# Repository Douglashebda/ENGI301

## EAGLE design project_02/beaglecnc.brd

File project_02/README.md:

**Board Prototype**

A PCB designed for the Desktop CNC design outlined here:

https://www.hackster.io/dah8/pocketbeagle-cnc-using-beagleg-070f2f

This board was designed for ENGI301 @RiceUni

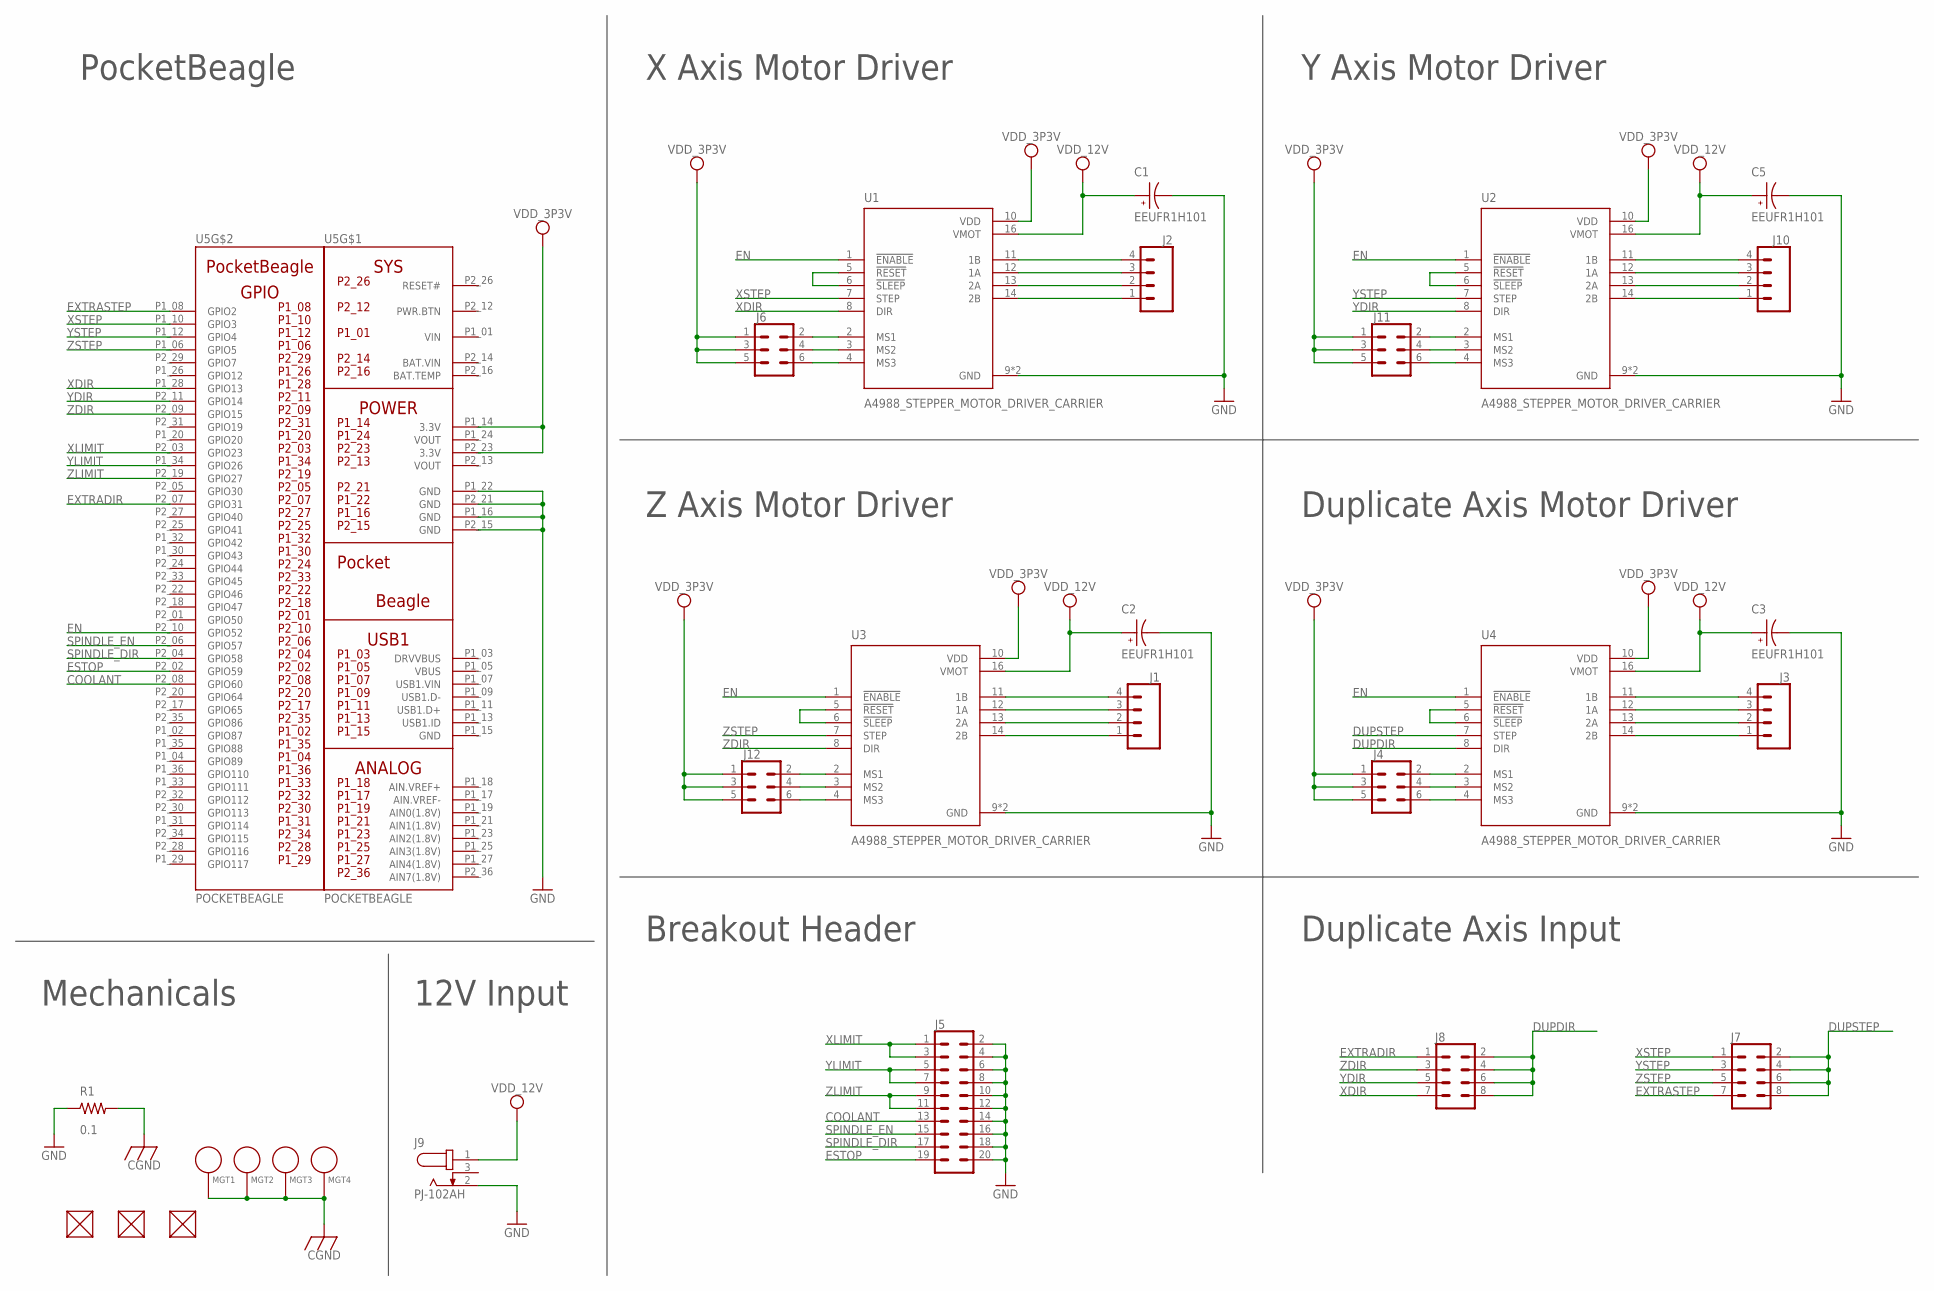
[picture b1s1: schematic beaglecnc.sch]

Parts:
C1, C2, C3, C5: EEUFR1H101; CAPPRD350W60D800H1150
FUD1, FUD2, FUD3: FIDUCIAL; FIDUCIAL_40MIL
J1, J2, J3, J10: CONN_04PTH; 1X04
J4, J6, J11, J12: CONN_03X22X3_SILK_MALE_PTH; 2X3
J5: CONN_10X2; 2X10
J7, J8: CONN_04X2; 2X4
J9: PJ-102AH; CUI_PJ-102AH
MGT1, MGT2, MGT3, MGT4: MOUNTING_HOLE
R1: 0.1; R0805
U1, U2, U3, U4: A4988_STEPPER_MOTOR_DRIVER_CARRIER; MODULE_A4988_STEPPER_MOTOR_DRIVER_CARRIER
U5: POCKETBEAGLE

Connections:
BAT.VIN: U5.P2_14 (BAT.VIN)
CGND: MGT1.P$1, MGT2.P$1, MGT3.P$1, MGT4.P$1, R1.2
COOLANT: J5.13, U5.P2_08 (GPIO60)
DUPDIR: J8.2, J8.4, J8.6, J8.8, U4.8 (DIR)
DUPSTEP: J7.2, J7.4, J7.6, J7.8, U4.7 (STEP)
EN: U1.1 (!ENABLE), U2.1 (!ENABLE), U3.1 (!ENABLE), U4.1 (!ENABLE), U5.P2_10 (GPIO52)
ESTOP: J5.19, U5.P2_02 (GPIO59)
EXTRADIR: J8.1, U5.P2_07 (GPIO31)
EXTRASTEP: J7.7, U5.P1_08 (GPIO2)
GND: C1.N, C2.N, C3.N, C5.N, J5.2, J5.4, J5.6, J5.8, J5.10, J5.12, J5.14, J5.16, J5.18, J5.20, J9.2, R1.1, U1.9 (GND), U1.15 (GND), U2.9 (GND), U2.15 (GND), U3.9 (GND), U3.15 (GND), U4.9 (GND), U4.15 (GND), U5.P1_16 (GND), U5.P1_22 (GND), U5.P2_15 (GND), U5.P2_21 (GND)
unnamed: J2.4, U1.11 (1B)
unnamed: J2.3, U1.12 (1A)
unnamed: J2.2, U1.13 (2A)
unnamed: J2.1, U1.14 (2B)
unnamed: U1.5 (!RESET), U1.6 (!SLEEP)
unnamed: J6.2, U1.2 (MS1)
unnamed: J6.4, U1.3 (MS2)
unnamed: J6.6, U1.4 (MS3)
unnamed: J10.4, U2.11 (1B)
unnamed: J10.3, U2.12 (1A)
unnamed: J10.2, U2.13 (2A)
unnamed: J10.1, U2.14 (2B)
unnamed: U2.5 (!RESET), U2.6 (!SLEEP)
unnamed: J11.2, U2.2 (MS1)
unnamed: J11.4, U2.3 (MS2)
unnamed: J11.6, U2.4 (MS3)
unnamed: J1.4, U3.11 (1B)
unnamed: J1.3, U3.12 (1A)
unnamed: J1.2, U3.13 (2A)
unnamed: J1.1, U3.14 (2B)
unnamed: U3.5 (!RESET), U3.6 (!SLEEP)
unnamed: J12.2, U3.2 (MS1)
unnamed: J12.4, U3.3 (MS2)
unnamed: J12.6, U3.4 (MS3)
unnamed: J3.4, U4.11 (1B)
unnamed: J3.3, U4.12 (1A)
unnamed: J3.2, U4.13 (2A)
unnamed: J3.1, U4.14 (2B)
unnamed: U4.5 (!RESET), U4.6 (!SLEEP)
unnamed: J4.2, U4.2 (MS1)
unnamed: J4.4, U4.3 (MS2)
unnamed: J4.6, U4.4 (MS3)
SPINDLE_DIR: J5.17, U5.P2_04 (GPIO58)
SPINDLE_EN: J5.15, U5.P2_06 (GPIO57)
VDD_3P3V: J4.1, J4.3, J4.5, J6.1, J6.3, J6.5, J11.1, J11.3, J11.5, J12.1, J12.3, J12.5, U1.10 (VDD), U2.10 (VDD), U3.10 (VDD), U4.10 (VDD), U5.P1_14 (3.3V), U5.P2_23 (3.3V)
VDD_12V: C1.P, C2.P, C3.P, C5.P, J9.1, U1.16 (VMOT), U2.16 (VMOT), U3.16 (VMOT), U4.16 (VMOT)
VIN: U5.P1_01 (VIN)
VOUT: U5.P1_24 (VOUT), U5.P2_13 (VOUT)
XDIR: J8.7, U1.8 (DIR), U5.P1_28 (GPIO13)
XLIMIT: J5.1, J5.3, U5.P2_03 (GPIO23)
XSTEP: J7.1, U1.7 (STEP), U5.P1_10 (GPIO3)
YDIR: J8.5, U2.8 (DIR), U5.P2_11 (GPIO14)
YLIMIT: J5.5, J5.7, U5.P1_34 (GPIO26)
YSTEP: J7.3, U2.7 (STEP), U5.P1_12 (GPIO4)
ZDIR: J8.3, U3.8 (DIR), U5.P2_09 (GPIO15)
ZLIMIT: J5.9, J5.11, U5.P2_19 (GPIO27)
ZSTEP: J7.5, U3.7 (STEP), U5.P1_06 (GPIO5)

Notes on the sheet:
PocketBeagle
X Axis Motor Driver
Y Axis Motor Driver
Duplicate Axis Motor Driver
Z Axis Motor Driver
Duplicate Axis Input
Breakout Header
12V Input
Mechanicals

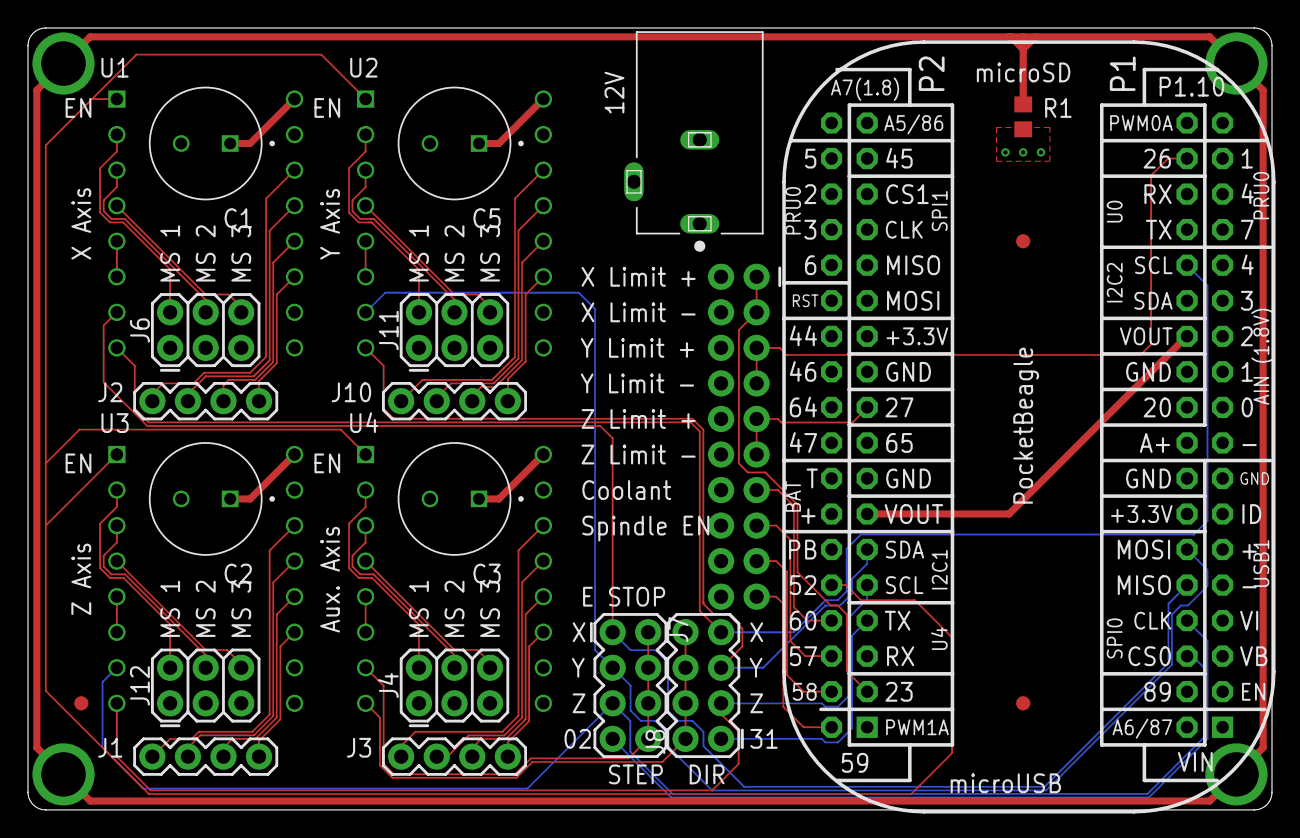
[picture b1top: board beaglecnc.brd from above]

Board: 4 copper layers, 88.9 x 55.9 mm, 29 parts (1 on the bottom side), 55 nets.

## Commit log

2021-10-05 Adding comments
2021-10-05 look mom i can code
2021-11-07 Create project_01
2021-11-08 Add files via upload
    Project Proposal with hardware budget and proposed software implementation.
2021-11-08 Initial project file commit
2021-12-14 Pdf of Schematic
